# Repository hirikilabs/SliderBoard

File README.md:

# SliderBoard

PCB para control de sliders y microsliders(macro) para fotografía.

## Documentación:

* Slider: https://lab.medialab.tabakalera.eus/proyecto/slider/
* Macro: https://lab.medialab.tabakalera.eus/proyecto/macrofotografia-extrema-automatizado/

## Firmwares:

* Control Slider: https://github.com/hirikilabs/AlbertoSlider
* Control Macro: https://github.com/hirikilabs/AlbertoMacro

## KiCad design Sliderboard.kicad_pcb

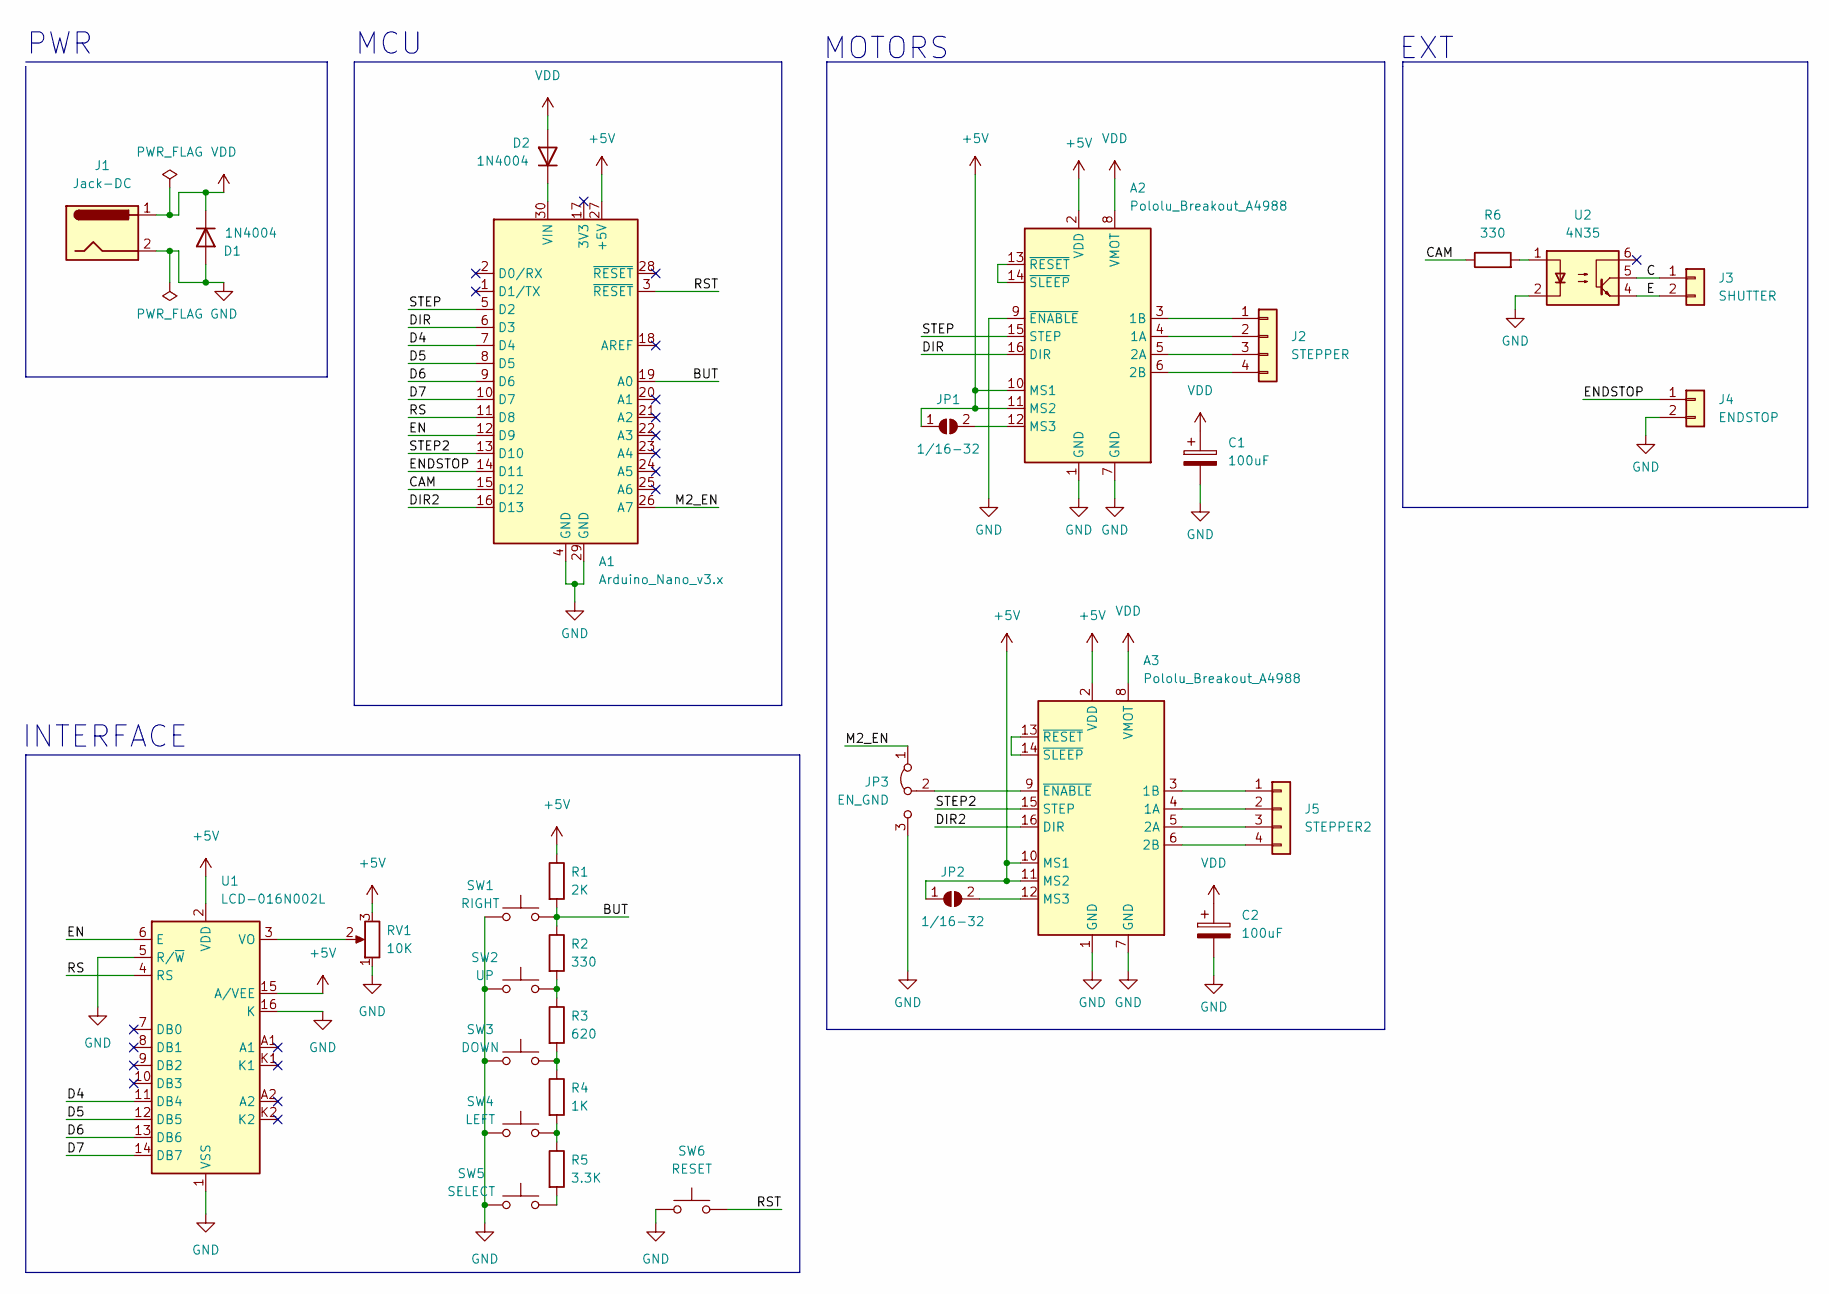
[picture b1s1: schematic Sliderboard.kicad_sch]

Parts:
A1: Arduino_Nano_v3.x; Arduino_Nano
A2, A3: Pololu_Breakout_A4988; Pololu_Breakout-16_15.2x20.3mm
C1, C2: 100uF; CP_Radial_D5.0mm_P2.00mm
D1, D2: 1N4004; D_DO-41_SOD81_P10.16mm_Horizontal
J1: Jack-DC; BarrelJack_Horizontal
J2: STEPPER; PinHeader_1x04_P2.54mm_Vertical
J3: SHUTTER; TerminalBlock_Phoenix_PT-1,5-2-3.5-H_1x02_P3.50mm_Horizontal
J4: ENDSTOP; TerminalBlock_Phoenix_PT-1,5-2-3.5-H_1x02_P3.50mm_Horizontal
J5: STEPPER2; PinHeader_1x04_P2.54mm_Vertical
JP1, JP2: 1/16-32; SolderJumper-2_P1.3mm_Open_RoundedPad1.0x1.5mm
JP3: EN_GND; SolderJumper-3_P1.3mm_Bridged2Bar12_RoundedPad1.0x1.5mm
R1: 2K; R_Axial_DIN0204_L3.6mm_D1.6mm_P7.62mm_Horizontal
R2, R6: 330; R_Axial_DIN0204_L3.6mm_D1.6mm_P7.62mm_Horizontal
R3: 620; R_Axial_DIN0204_L3.6mm_D1.6mm_P7.62mm_Horizontal
R4: 1K; R_Axial_DIN0204_L3.6mm_D1.6mm_P7.62mm_Horizontal
R5: 3.3K; R_Axial_DIN0204_L3.6mm_D1.6mm_P7.62mm_Horizontal
RV1: 10K; Potentiometer_Piher_PT-6-V_Vertical
SW1: RIGHT; SW_PUSH_6mm
SW2: UP; SW_PUSH_6mm
SW3: DOWN; SW_PUSH_6mm
SW4: LEFT; SW_PUSH_6mm
SW5: SELECT; SW_PUSH_6mm
SW6: RESET; SW_PUSH_6mm
U1: LCD-016N002L; WC1602A
U2: 4N35; DIP-6_W7.62mm

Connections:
+5V: A1.27 (+5V), A2.2 (VDD), A2.10 (MS1), A2.11 (MS2), A3.2 (VDD), A3.10 (MS1), A3.11 (MS2), JP1.1 (A), JP2.1 (A), R1.1, RV1.3, U1.2 (VDD), U1.15 (A/VEE)
/BUT: A1.19 (A0), R1.2, R2.1, SW1.2
/C: J3.1, U2.5
/CAM: A1.15 (D12), R6.1
/D4: A1.7 (D4), U1.11 (DB4)
/D5: A1.8 (D5), U1.12 (DB5)
/D6: A1.9 (D6), U1.13 (DB6)
/D7: A1.10 (D7), U1.14 (DB7)
/DIR: A1.6 (D3), A2.16 (DIR)
/DIR2: A1.16 (D13), A3.16 (DIR)
/E: J3.2, U2.4
/EN: A1.12 (D9), U1.6 (E)
/ENDSTOP: A1.14 (D11), J4.1
/M2_EN: A1.26 (A7), JP3.1 (A)
/RS: A1.11 (D8), U1.4 (RS)
/RST: A1.3 (~RESET), SW6.2
/STEP: A1.5 (D2), A2.15 (STEP)
/STEP2: A1.13 (D10), A3.15 (STEP)
GND: A1.4 (GND), A1.29 (GND), A2.1 (GND), A2.7 (GND), A2.9 (~ENABLE), A3.1 (GND), A3.7 (GND), C1.2, C2.2, D1.2 (A), J1.2, J4.2, JP3.3 (B), RV1.1, SW1.1, SW2.1, SW3.1, SW4.1, SW5.1, SW6.1, U1.1 (VSS), U1.5 (R/~W), U1.16 (K), U2.2
unnamed: A1.30 (VIN), D2.1 (K)
unnamed: A2.3 (1B), J2.1
unnamed: A2.4 (1A), J2.2
unnamed: A2.5 (2A), J2.3
unnamed: A2.6 (2B), J2.4
unnamed: A2.12 (MS3), JP1.2 (B)
unnamed: A2.13 (~RESET), A2.14 (~SLEEP)
unnamed: A3.3 (1B), J5.1
unnamed: A3.4 (1A), J5.2
unnamed: A3.5 (2A), J5.3
unnamed: A3.6 (2B), J5.4
unnamed: A3.9 (~ENABLE), JP3.2 (C)
unnamed: A3.12 (MS3), JP2.2 (B)
unnamed: A3.13 (~RESET), A3.14 (~SLEEP)
unnamed: R2.2, R3.1, SW2.2
unnamed: R3.2, R4.1, SW3.2
unnamed: R4.2, R5.1, SW4.2
unnamed: R5.2, SW5.2
unnamed: R6.2, U2.1
unnamed: RV1.2, U1.3 (VO)
VDD: A2.8 (VMOT), A3.8 (VMOT), C1.1, C2.1, D1.1 (K), D2.2 (A), J1.1

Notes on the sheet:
MCU
INTERFACE
EXT
MOTORS
PWR

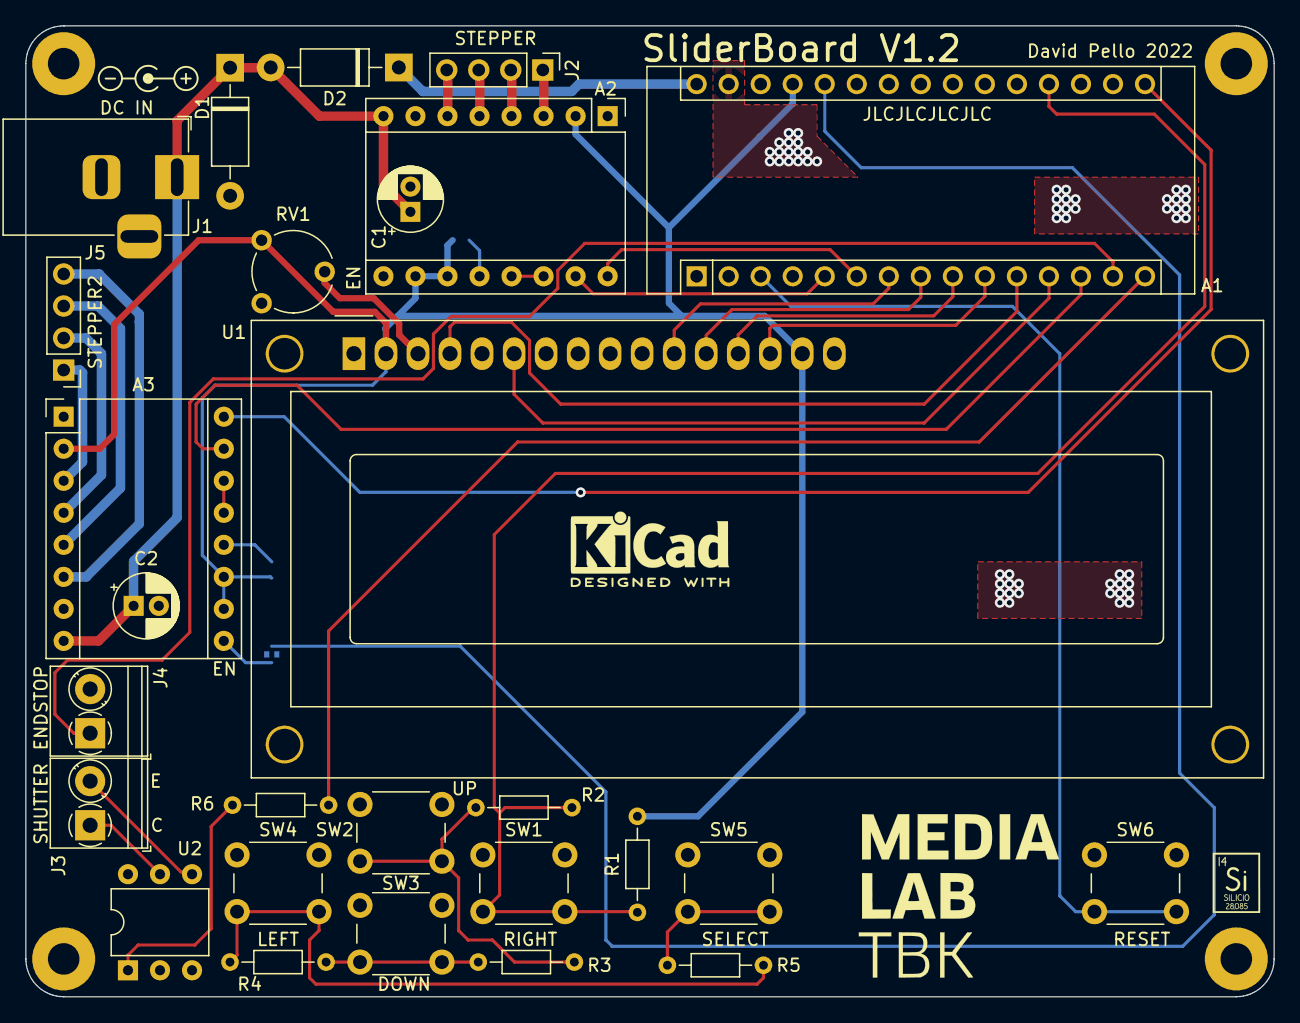
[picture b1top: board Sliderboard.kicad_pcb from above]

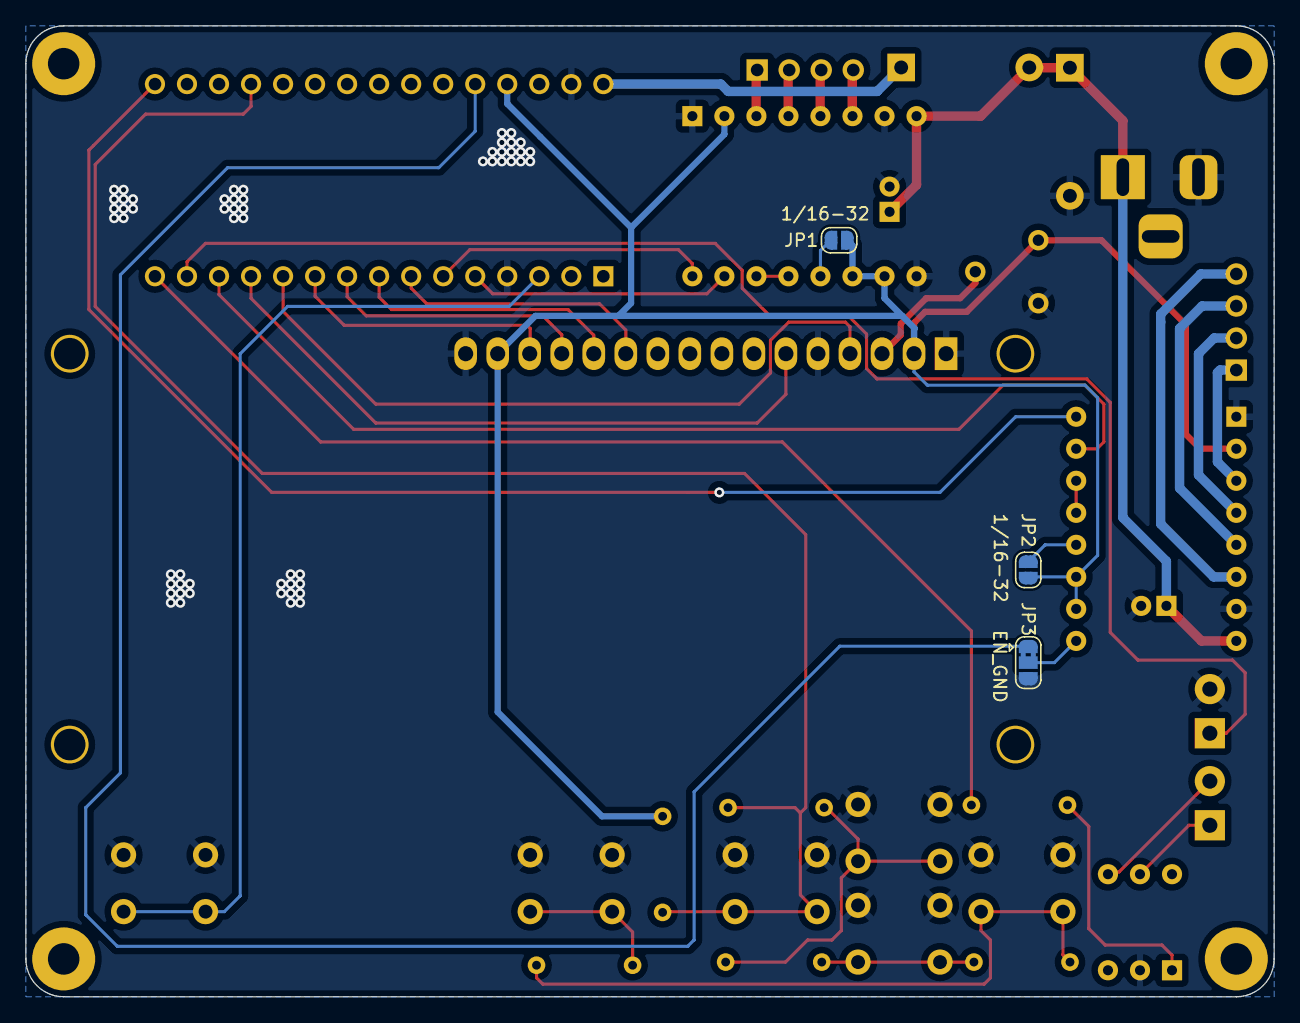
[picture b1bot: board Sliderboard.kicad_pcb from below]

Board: 2 copper layers, 99.0 x 77.0 mm, 30 parts (3 on the bottom side), 40 nets.

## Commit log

2023-02-13 initial import
